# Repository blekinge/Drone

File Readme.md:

# Seminarprogram: **Arduino Pilot** (ESP32 + GPS, Servo, PWM, ESP-NOW)

> **Målgruppe:** Udviklings-, test- og prototyping-ingeniører samt avancerede hobbyister.
>
> **Resultat:** Indsigt i bygning af en fungerende “pilot”-controller på ESP32, der modtager kommandoer via ESP-NOW, styrer servo (ror) og motor (PWM), læser strøm/spænding fra INA219 og GPS-data, og udsender telemetri via ESP-NOW.

---

## Læringsmål
1. Forstå arkitekturen i en simpel “pilot” på ESP32 (sensorer → styring → aktuatorer → telemetri).
2. Opsætte og bruge I²C (INA219), UART (GPS), PWM/LEDC (motor), og servo-styring (PWM) på ESP32.
3. Kende ESP-NOW til lav-latens en-til-en/mesh/broadcast kommunikation uden AP.
4. Designe en robust datapakke (kommando/telemetri) og testprocedurer.
5. Anvende bedste praksis for strømforsyning, jording, EMI og failsafe.
6. ArduPilot implementation

---

## Forudsætninger
- Basal C/C++ og Arduino-IDE/PlatformIO-kendskab.
- Kendskab til multimeter/oscilloskop anbefales.
- Installeret: **Arduino IDE (2.x)** eller **PlatformIO**, ESP32 board support, biblioteker: *Adafruit INA219*, *TinyGPSPlus*, *ESP32Servo*.

---

## Udstyrsliste (pr. deltager/gruppe)
- ESP32-WROOM-32 dev board + USB-kabel.
- INA219B modul (I²C shunt-måler) **SDA=23, SCL=22**
- GPS-modul (fx NEO-6M) på **UART2 RX=16, TX=17** @ 9600 baud.
- Mikroservo (fx SG90) på **GPIO14** (separat 5V, fælles GND).
- PWM motor/ESC/controller på **GPIO4** (LEDC PWM).
- 3× LED med seriemodstande på **GPIO 12, 13, 15**.
- Strømforsyning 5V/2A (servo/motor), breadboard, ledninger, evt. step-down.

## Schematic

- [Modtager schematic](https://github.com/gert-lauritsen/Drone/blob/main/PCB/Modtager/TocBoatReceiver.pdf)

- [Sender Schematic](https://github.com/gert-lauritsen/Drone/blob/main/PCB/Sender/RcSender.pdf)

## Datapakker (reference)
```c
// Kommandoer (ESP-NOW → pilot)
typedef struct __attribute__((packed)) {
  uint16_t servo_us;   // 1000..2000 µs typisk
  uint16_t motor_duty; // 0..1023 ved 10-bit LEDC
  uint8_t  leds;       // bit0=GPIO12, bit1=GPIO13, bit2=GPIO15
} CommandPacket;

// Telemetri (pilot → ESP-NOW)
typedef struct __attribute__((packed)) {
  float    busV;      // V
  float    shuntV;    // mV
  float    current_mA;// mA
  float    power_mW;  // mW
  double   lat;       // °
  double   lon;       // °
  float    speed_kmh; // km/h
  uint8_t  sats;      // antal satellitter
  uint32_t fixAge_ms; // ms siden sidste fix
} TelemetryPacket;
```

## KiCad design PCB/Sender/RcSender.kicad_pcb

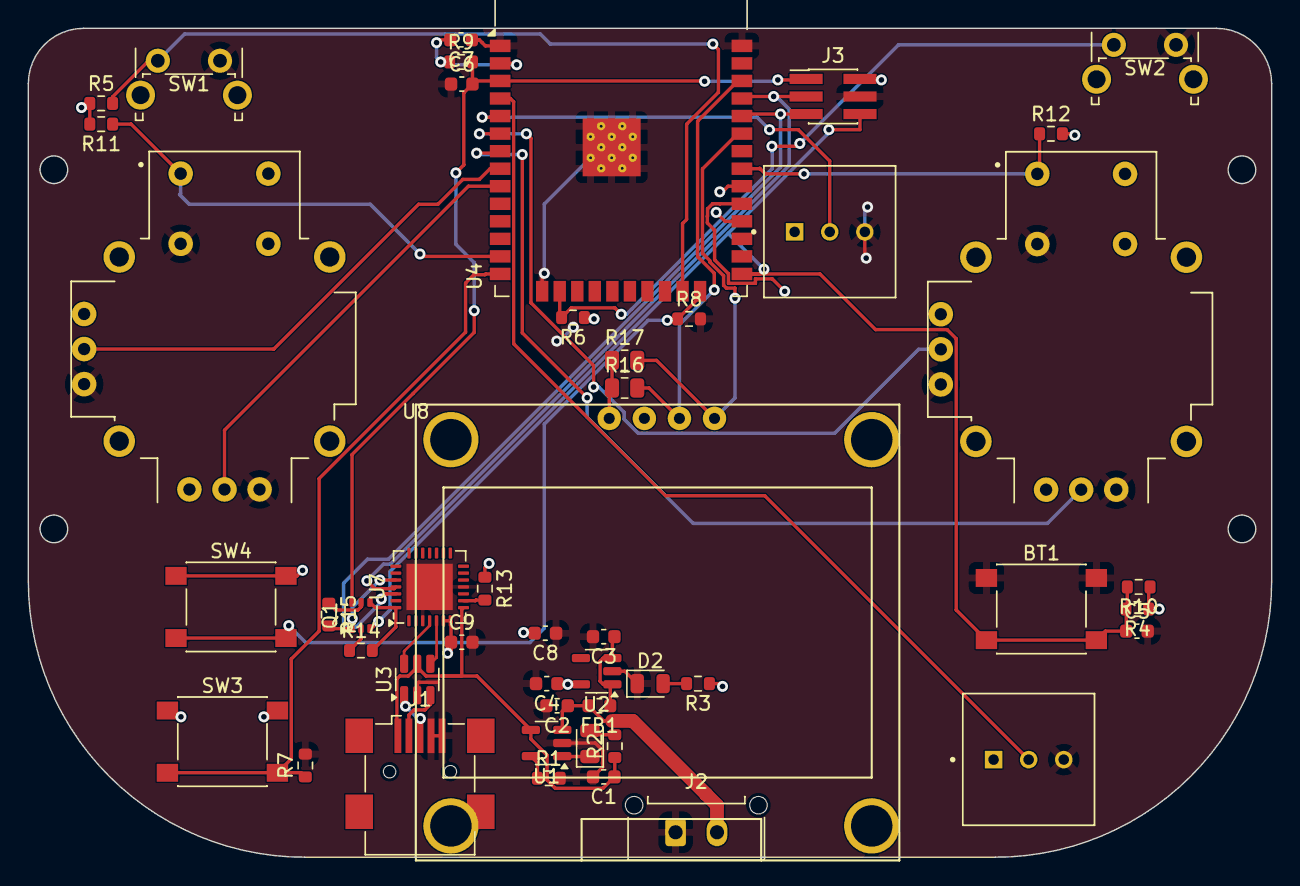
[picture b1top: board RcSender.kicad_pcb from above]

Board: 2 copper layers, 90.0 x 60.0 mm, 48 parts (0 on the bottom side), 37 nets.

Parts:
BT1: SW_Push; SW_SPST_PTS645
C1, C3, C4: 1uF; C_0603_1608Metric
C2: 10nF; C_0603_1608Metric
C5, C6, C7, C8: 0.1uf; C_0603_1608Metric
C9: 10u; C_0603_1608Metric
D1: Chrg; LED_0805_2012Metric
D2: PWR ON; LED_0805_2012Metric
FB1: Ferrite Bead; L_0603_1608Metric
J1: USB_A; USB_Mini-B_Wuerth_65100516121_Horizontal
J2: Bat; Molex_Micro-Fit_3.0_43650-0215_1x02_P3.00mm_Vertical
J3: Prog; PinHeader_2x03_P1.27mm_Vertical_SMD
POT1, POT2: COM-09806; POT-COM_09806
Q1: BC846BS; SOT-363_SC-70-6
R1: 2k; R_0603_1608Metric
R2, R3: 330; R_0603_1608Metric
R4, R5, R6, R7, R8, R11, R12: 4.7k; R_0603_1608Metric
R9, R10: 10K; R_0603_1608Metric
R13: 1k; R_0603_1608Metric
R14, R15: 10k; R_0603_1608Metric
R16, R17: 10k; R_0805_2012Metric
SW1, SW2: SW_Push; SW_Tactile_SPST_Angled_PTS645Vx39-2LFS
SW3, SW4: SW_Push; SW_SPST_PTS645
U1: MCP73832-2-OT; SOT-23-5
U2: AP2112K-3.3; SOT-23-5
U3: USBLC6-2SC6; SOT-23-6
U4: ESP32-WROOM-32
U5, U6: COM-09032; POT-COM-09032
U7: CP2102N-Axx-xQFN28; QFN-28-1EP_5x5mm_P0.5mm_EP3.35x3.35mm
U8: OLED128x64; 1.3 IIC display

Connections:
+3.3V: C4.1, C7.2, C8.2, C9.1, J3.2, POT1.1, POT2.1, R3.1, R4.1, R5.1, R6.1, R9.1, R10.1, R11.2, R12.2, R13.1, SW3.1, SW4.1, U2.5 (VOUT), U4.2 (VDD), U5.H1 (H+), U5.V1 (V+), U6.H1 (H+), U6.V1 (V+), U7.6 (VDD), U7.7 (VREGIN)
+3V3: R16.1, R17.1, U8.1 (VCC)
+5V: C1.1, J1.1 (VBUS), R2.1, U1.4 (V_{DD}), U3.5 (VBUS), U7.8 (VBUS)
BT: BT1.2, C5.1, J3.6, Q1.3 (C2), R4.2, R10.2, U4.25 (IO0)
EN: C6.2, J3.1, Q1.6 (C1), R9.2, U4.3 (EN)
GND: BT1.1, C1.2, C2.2, C3.2, C4.2, C5.2, C6.1, C7.1, C8.1, C9.2, D2.1 (K), J1.4 (GND), J1.5 (Shield), J2.1, J3.4, POT1.3, POT2.3, R1.2, R7.2, R8.2, SW1.2, SW2.2, U1.2 (V_{SS}), U2.2 (GND), U3.2 (GND), U4.1 (GND), U4.15 (GND), U4.38 (GND), U4.39 (GND), U5.B2A (SEL-), U5.H3 (H-), U5.V3 (V-), U6.B2A (SEL-), U6.H3 (H-), U6.V3 (V-), U7.3 (GND), U7.11 (~SUSPEND), U7.29 (GND)
IO2: R8.1, SW4.2, U4.24 (IO2)
IO12: R7.1, SW3.2, U4.14 (IO12)
IO13: R6.2, SW2.1, U4.16 (IO13)
IO14: R11.1, U4.13 (IO14), U5.B1A (SEL+)
IO15: R5.2, SW1.1, U4.23 (IO15)
IO19: R12.1, U4.31 (IO19), U6.B1A (SEL+)
IO32: U4.8 (IO32), U5.V2 (V)
IO33: U4.9 (IO33), U5.H2 (H)
IO34: U4.6 (IO34), U6.V2 (V)
IO35: U4.7 (IO35), U6.H2 (H)
IO36: POT1.2, U4.4 (SENSOR_VP)
IO39: POT2.2, U4.5 (SENSOR_VN)
unnamed: D1.2 (A), R2.2
unnamed: D1.1 (K), U1.1 (STAT)
unnamed: D2.2 (A), R3.2
unnamed: J1.3 (D+), U3.1 (I/O1)
unnamed: J1.2 (D-), U3.3 (I/O2)
unnamed: Q1.2 (B1), R14.1
unnamed: Q1.1 (E1), R15.2, U7.24 (~RTS)
unnamed: Q1.5 (B2), R15.1
unnamed: Q1.4 (E2), R14.2, U7.28 (~DTR)
unnamed: R1.1, U1.5 (PROG)
unnamed: C3.1, FB1.1, U2.1 (VIN), U2.3 (EN)
unnamed: R13.2, U7.9 (~RST)
RX: J3.5, U4.34 (RXD0/IO3), U7.26 (TXD)
SCL: R16.2, U4.36 (IO22), U8.3 (SCL)
SDA: R17.2, U4.33 (IO21), U8.4 (SDA)
TX: J3.3, U4.35 (TXD0/IO1), U7.25 (RXD)
USBN: U3.4 (I/O2), U7.5 (D-)
USBP: U3.6 (I/O1), U7.4 (D+)
VIN: C2.1, FB1.2, J2.2, U1.3 (V_{BAT})

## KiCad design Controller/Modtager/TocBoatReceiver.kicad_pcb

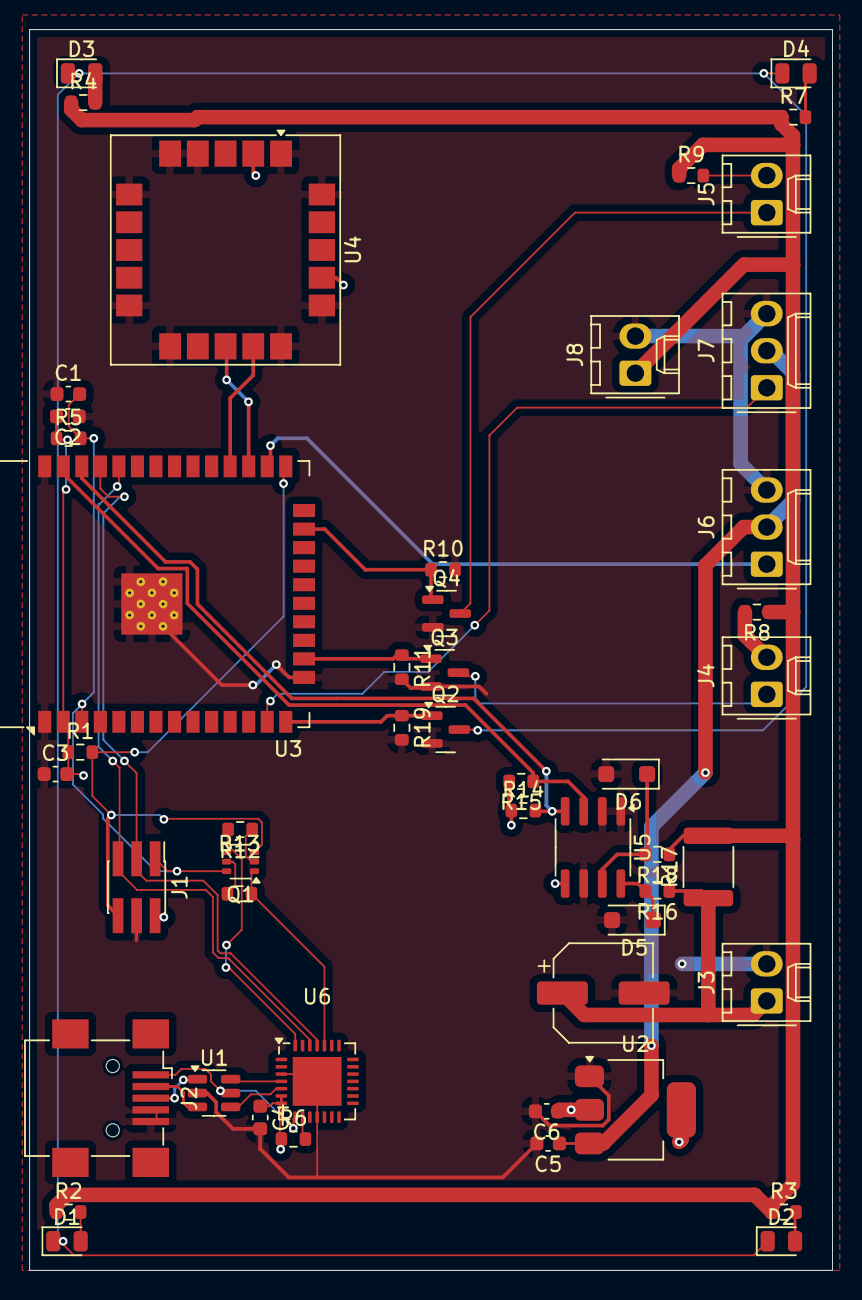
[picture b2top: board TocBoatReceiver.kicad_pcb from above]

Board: 2 copper layers, 55.0 x 85.0 mm, 50 parts (0 on the bottom side), 39 nets.

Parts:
C1, C2, C3: 0.1uf; C_0603_1608Metric
C4: 10u; C_0603_1608Metric
C5, C6: 1u; C_0603_1608Metric
C7: 100uF; CP_Elec_6.3x5.4
D1, D2, D3, D4: LED; LED_0805_2012Metric
D5, D6: BZT52B-C20; D_SOD-123F
J1: Prog; PinHeader_2x03_P1.27mm_Vertical_SMD
J2: USB_A; USB_Mini-B_Wuerth_65100516121_Horizontal
J3: Battery; Molex_KK-254_AE-6410-02A_1x02_P2.54mm_Vertical
J4, J5: Conn_01x02; Molex_KK-254_AE-6410-02A_1x02_P2.54mm_Vertical
J6: SpeedController; Molex_KK-254_AE-6410-03A_1x03_P2.54mm_Vertical
J7: Servo; Molex_KK-254_AE-6410-03A_1x03_P2.54mm_Vertical
J8: PowerESC; Molex_KK-254_AE-6410-02A_1x02_P2.54mm_Vertical
Q1: BC846BS; SOT-363_SC-70-6
Q2, Q3, Q4: AO3400A; SOT-23
R1, R5, R10, R11, R14, R15, R19: 10K; R_0603_1608Metric
R2, R3, R4, R6, R7, R8, R9: 1k; R_0603_1608Metric
R12, R13: 10k; R_0603_1608Metric
R16, R18: 100; R_0603_1608Metric
R17: 0.01R; R_1812_4532Metric
U1: USBLC6-2SC6; SOT-23-6
U2: AP1117-33; SOT-223-3_TabPin2
U3: ESP32-WROOM-32
U4: SAM-M8Q; ublox_SAM-M8Q
U5: INA219BxD; SOIC-8_3.9x4.9mm_P1.27mm
U6: CP2102N-Axx-xQFN28; QFN-28-1EP_5x5mm_P0.5mm_EP3.35x3.35mm

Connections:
+3.3V: C2.2, C3.2, C4.1, C6.1, J1.2, R1.1, R5.1, R6.1, R14.1, R15.2, U2.2 (VO), U3.2 (VDD), U4.2 (VCC_IO), U4.17 (VCC), U5.5 (VS), U6.6 (VDD), U6.7 (VREGIN)
+5V: J2.1 (VBUS), U1.5 (VBUS), U6.8 (VBUS)
+BATT: J8.1, R2.1, R3.1, R4.1, R7.1, R8.1, R9.1, R17.2, R18.1
/ESP32/GPIO4: J6.1, U3.26 (IO4)
/ESP32/GPIO12: Q2.1 (G), R19.1, U3.14 (IO12)
/ESP32/GPIO13: Q3.1 (G), R11.1, U3.16 (IO13)
/ESP32/GPIO14: J7.1, U3.13 (IO14)
/ESP32/GPIO15: Q4.1 (G), R10.1, U3.23 (IO15)
/ESP32/GPIO16: U3.27 (IO16), U4.13 (TXD)
/ESP32/GPIO17: U3.28 (IO17), U4.14 (RXD)
/ESP32/SCL: R14.2, U3.36 (IO22), U5.4 (SCL)
/ESP32/SDA: R15.1, U3.37 (IO23), U5.3 (SDA)
/USB Serial/USB_N: U1.4 (I/O2), U6.5 (D-)
/USB Serial/USB_P: U1.6 (I/O1), U6.4 (D+)
D0: J1.6, Q1.3 (C2), R1.2, U3.25 (IO0)
EN: C1.2, J1.1, Q1.6 (C1), R5.2, U3.3 (EN)
GND: C1.1, C2.1, C3.1, C4.2, C5.2, C6.2, C7.2, D5.2 (A), D6.2 (A), J1.4, J2.4 (GND), J2.5 (Shield), J3.2, J6.3, J7.3, J8.2, Q2.2 (S), Q3.2 (S), Q4.2 (S), R10.2, R11.2, R19.2, U1.2 (GND), U2.1 (GND), U3.1 (GND), U3.15 (GND), U3.38 (GND), U3.39 (GND), U4.1 (GND), U4.4 (GND), U4.5 (GND), U4.6 (GND), U4.10 (GND), U4.11 (GND), U4.15 (GND), U4.16 (GND), U4.20 (GND), U5.1 (A1), U5.2 (A0), U5.6 (GND), U6.3 (GND), U6.11 (~SUSPEND), U6.29 (GND)
unnamed: D1.2 (A), R2.2
unnamed: D1.1 (K), D2.1 (K), D3.1 (K), D4.1 (K), Q2.3 (D)
unnamed: D2.2 (A), R3.2
unnamed: D3.2 (A), R4.2
unnamed: D4.2 (A), R7.2
unnamed: D5.1 (K), R16.2, U5.8 (IN+)
unnamed: D6.1 (K), R18.2, U5.7 (IN-)
unnamed: J2.3 (D+), U1.1 (I/O1)
unnamed: J2.2 (D-), U1.3 (I/O2)
unnamed: C7.1, J3.1, R16.1, R17.1
unnamed: J4.1, Q3.3 (D)
unnamed: J4.2, R8.2
unnamed: J5.1, Q4.3 (D)
unnamed: J5.2, R9.2
unnamed: Q1.2 (B1), R12.1
unnamed: Q1.1 (E1), R13.2, U6.24 (~RTS)
unnamed: Q1.5 (B2), R13.1
unnamed: Q1.4 (E2), R12.2, U6.28 (~DTR)
unnamed: R6.2, U6.9 (~RST)
RX: J1.5, U3.34 (RXD0/IO3), U6.26 (TXD)
TX: J1.3, U3.35 (TXD0/IO1), U6.25 (RXD)
VDC: C5.1, J6.2, J7.2, U2.3 (VI)

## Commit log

2025-10-04 init
2025-10-05 hul igennem til modtager
2025-10-05 kontakt til sender
2025-10-06 dual pwm fungere
2025-10-07 data gennem til ardupilot
